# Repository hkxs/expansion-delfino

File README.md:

# expansion-delfino
Tarjeta de expansión para el launchpad LAUNCHXL-F28377S

Para un tutorial rápido sobre el MCU TMS320F28377S se puede consultar:

http://odin.fi-b.unam.mx/labdsp/files/ADSP/apuntes/Tutorial_VF.pdf

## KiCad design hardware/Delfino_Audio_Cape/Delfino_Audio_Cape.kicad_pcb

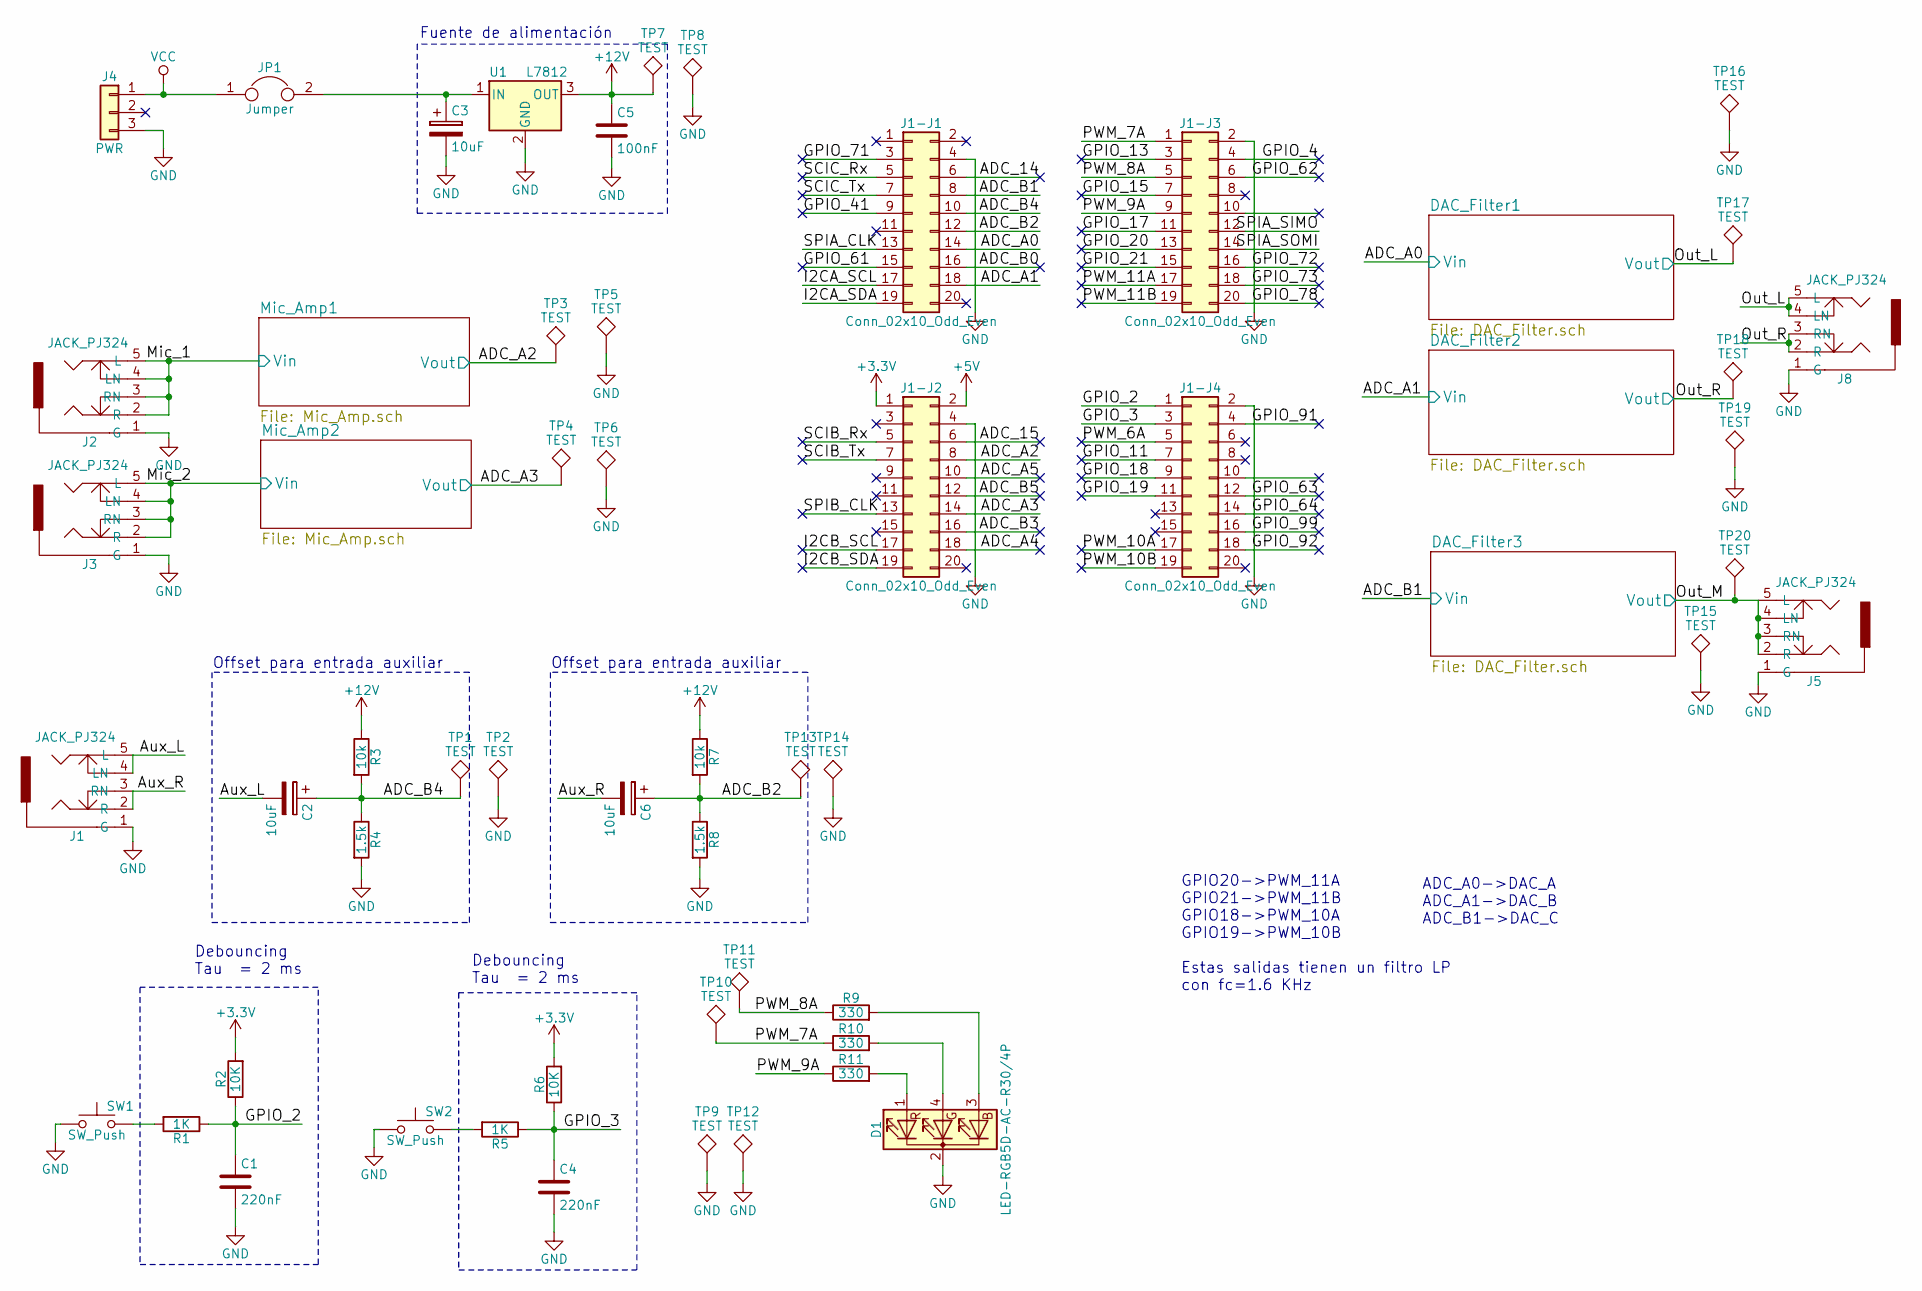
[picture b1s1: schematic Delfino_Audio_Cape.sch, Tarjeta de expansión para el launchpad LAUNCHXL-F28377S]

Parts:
C1, C4: 220nF; C_Disc_D4.3mm_W1.9mm_P5.00mm
C2, C3, C6: 10uF; CP_Radial_D6.3mm_P2.50mm
C5: 100nF; C_Disc_D4.3mm_W1.9mm_P5.00mm
D1: LED-RGB5D-AC-R30/4P; LED_D5.0mm-4
J1, J2, J3, J5, J8: JACK_PJ324; PJ-324
J1-J1, J1-J2, J1-J3, J1-J4: Conn_02x10_Odd_Even; Pin_Header_Straight_2x10_Pitch2.54mm
J4: PWR; bornier3
JP1: Jumper; Pin_Header_Straight_1x02_Pitch2.54mm
R1, R5: 1K; R_Axial_DIN0207_L6.3mm_D2.5mm_P10.16mm_Horizontal
R2, R6: 10K; R_Axial_DIN0207_L6.3mm_D2.5mm_P10.16mm_Horizontal
R3, R7: 10k; R_Axial_DIN0207_L6.3mm_D2.5mm_P10.16mm_Horizontal
R4, R8: 1.5k; R_Axial_DIN0207_L6.3mm_D2.5mm_P10.16mm_Horizontal
R9, R10, R11: 330; R_Axial_DIN0207_L6.3mm_D2.5mm_P10.16mm_Horizontal
SW1, SW2: SW_Push; SW_PUSH_6mm
TP1, TP2, TP3, TP4, TP5, TP6, TP7, TP8, TP9, TP10, TP11, TP12, TP13, TP14, TP15, TP16, TP17, TP18, TP19, TP20: TEST; Test_Point_THTPad_4.0x4.0mm_Drill2.0mm
U1: L7812; TO-220_Horizontal

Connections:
+3V3: J1-J2.1, R2.2, R6.2
+5V: J1-J2.2
+12V: C5.1, R3.1, R7.1, TP7.1, U1.3 (OUT); also elsewhere on the board
/ADC_14: J1-J1.6
/ADC_15: J1-J2.6
/ADC_A0: J1-J1.14; also elsewhere on the board
/ADC_A1: J1-J1.18; also elsewhere on the board
/ADC_A2: J1-J2.8, TP3.1; also elsewhere on the board
/ADC_A3: J1-J2.14, TP4.1; also elsewhere on the board
/ADC_A4: J1-J2.18
/ADC_A5: J1-J2.10
/ADC_B0: J1-J1.16
/ADC_B1: J1-J1.8; also elsewhere on the board
/ADC_B2: C6.1, J1-J1.12, R7.2, R8.1, TP13.1
/ADC_B3: J1-J2.16
/ADC_B4: C2.1, J1-J1.10, R3.2, R4.1, TP1.1
/ADC_B5: J1-J2.12
/Aux_L: C2.2, J1.4 (LN), J1.5 (L)
/Aux_R: C6.2, J1.2 (R), J1.3 (RN)
/GPIO_2: C1.1, J1-J4.1, R1.1, R2.1
/GPIO_3: C4.1, J1-J4.3, R5.1, R6.1
/GPIO_4: J1-J3.4
/GPIO_11: J1-J4.7
/GPIO_13: J1-J3.3
/GPIO_15: J1-J3.7
/GPIO_17: J1-J3.11
/GPIO_18: J1-J4.9
/GPIO_19: J1-J4.11
/GPIO_20: J1-J3.13
/GPIO_21: J1-J3.15
/GPIO_41: J1-J1.9
/GPIO_61: J1-J1.15
/GPIO_62: J1-J3.6
/GPIO_63: J1-J4.12
/GPIO_64: J1-J4.14
/GPIO_71: J1-J1.3
/GPIO_72: J1-J3.16
/GPIO_73: J1-J3.18
/GPIO_78: J1-J3.20
/GPIO_91: J1-J4.4
/GPIO_92: J1-J4.18
/GPIO_99: J1-J4.16
/I2CA_SCL: J1-J1.17
/I2CA_SDA: J1-J1.19
/I2CB_SCL: J1-J2.17
/I2CB_SDA: J1-J2.19
/Mic_1: J2.2 (R), J2.3 (RN), J2.4 (LN), J2.5 (L); also elsewhere on the board
/Mic_2: J3.2 (R), J3.3 (RN), J3.4 (LN), J3.5 (L); also elsewhere on the board
/Out_L: J8.4 (LN), J8.5 (L), TP17.1; also elsewhere on the board
/Out_M: J5.2 (R), J5.3 (RN), J5.4 (LN), J5.5 (L), TP20.1; also elsewhere on the board
/Out_R: J8.2 (R), J8.3 (RN), TP18.1; also elsewhere on the board
/PWM_6A: J1-J4.5
/PWM_7A: J1-J3.1, R10.1, TP10.1
/PWM_8A: J1-J3.5, R9.1, TP11.1
/PWM_9A: J1-J3.9, R11.1
/PWM_10A: J1-J4.17
/PWM_10B: J1-J4.19
/PWM_11A: J1-J3.17
/PWM_11B: J1-J3.19
/SCIB_Rx: J1-J2.5
/SCIB_Tx: J1-J2.7
/SCIC_Rx: J1-J1.5
/SCIC_Tx: J1-J1.7
/SPIA_CLK: J1-J1.13
/SPIA_SIMO: J1-J3.12
/SPIA_SOMI: J1-J3.14
/SPIB_CLK: J1-J2.13
GND: C1.2, C3.2, C4.2, C5.2, D1.2 (K), J1.1 (G), J1-J1.4, J1-J2.4, J1-J3.2, J1-J4.2, J2.1 (G), J3.1 (G), J4.3, J5.1 (G), J8.1 (G), R4.2, R8.2, SW1.1, SW2.1, TP2.1, TP5.1, TP6.1, TP8.1, TP9.1, TP12.1, TP14.1, TP15.1, TP16.1, TP19.1, U1.2 (GND); also elsewhere on the board
unnamed: C3.1, JP1.2, U1.1 (IN)
unnamed: D1.1 (RA), R11.2
unnamed: D1.3 (BA), R9.2
unnamed: D1.4 (GA), R10.2
unnamed: R1.2, SW1.2
unnamed: R5.2, SW2.2
VCC: J4.1, JP1.1

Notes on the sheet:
ADC_A0->DAC_A ADC_A1->DAC_B ADC_B1->DAC_C
GPIO20->PWM_11A GPIO21->PWM_11B GPIO18->PWM_10A GPIO19->PWM_10B Estas salidas tienen un filtro LP con fc=1.6 KHz
Debouncing Tau = 2 ms
Offset para entrada auxiliar
Fuente de alimentación

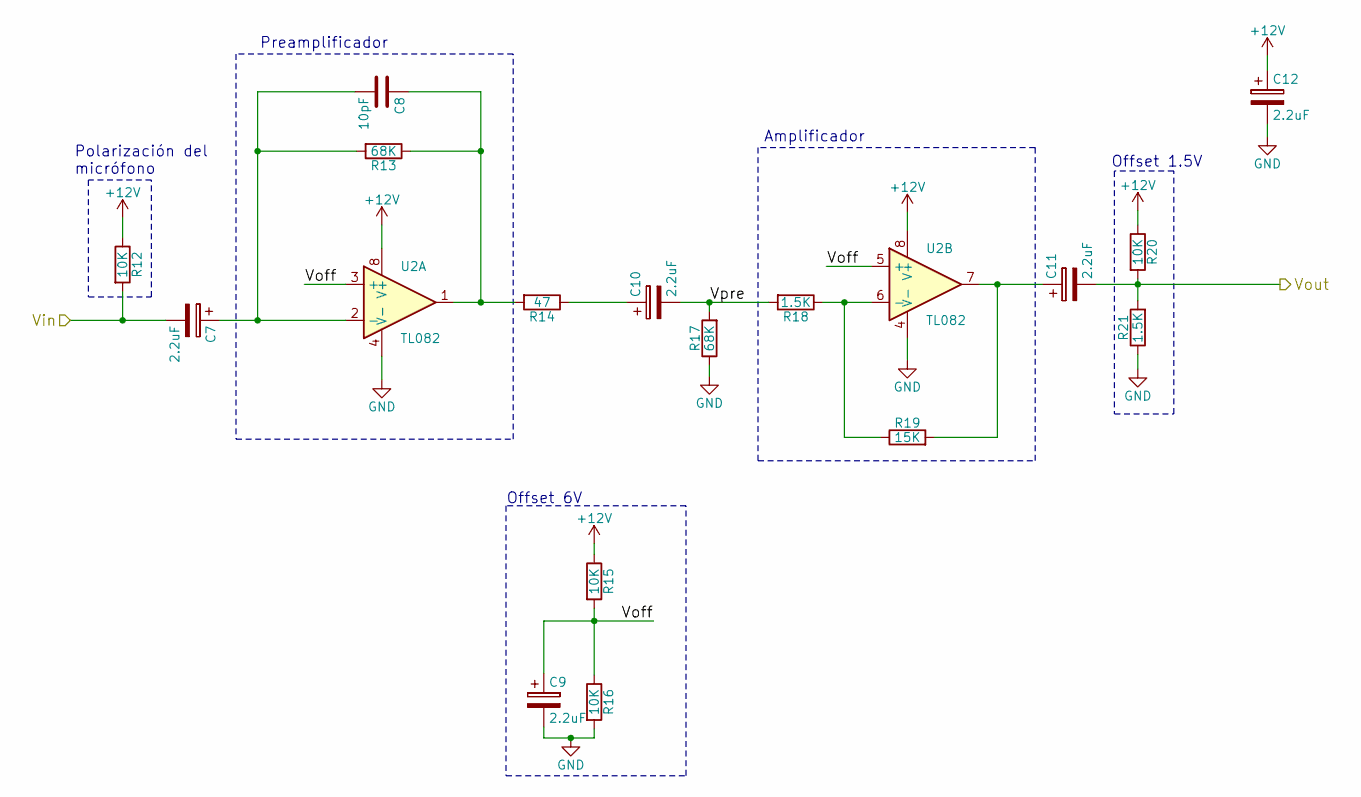
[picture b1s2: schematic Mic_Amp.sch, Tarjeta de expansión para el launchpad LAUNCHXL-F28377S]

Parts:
C7, C9, C10, C11, C12: 2.2uF; CP_Radial_D6.3mm_P2.50mm
C8: 10pF; C_Disc_D4.3mm_W1.9mm_P5.00mm
R12, R15, R16, R20: 10K; R_Axial_DIN0207_L6.3mm_D2.5mm_P10.16mm_Horizontal
R13, R17: 68K; R_Axial_DIN0207_L6.3mm_D2.5mm_P10.16mm_Horizontal
R14: 47; R_Axial_DIN0207_L6.3mm_D2.5mm_P10.16mm_Horizontal
R18, R21: 1.5K; R_Axial_DIN0207_L6.3mm_D2.5mm_P10.16mm_Horizontal
R19: 15K; R_Axial_DIN0207_L6.3mm_D2.5mm_P10.16mm_Horizontal
U2: TL082; DIP-8_W7.62mm_LongPads

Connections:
+12V: C12.1, R12.1, R15.1, R20.1, U2.8 (V+); also elsewhere on the board
/ADC_A2: C11.2, R20.2, R21.2; also elsewhere on the board
/Mic_1: C7.2, R12.2; also elsewhere on the board
/Mic_Amp1/Voff: C9.1, R15.2, R16.1, U2.3 (+), U2.5 (+)
/Mic_Amp1/Vpre: C10.2, R17.2, R18.2
GND: C9.2, C12.2, R16.2, R17.1, R21.1, U2.4 (V-); also elsewhere on the board
unnamed: C7.1, C8.2, R13.2, U2.2 (-)
unnamed: C8.1, R13.1, R14.2, U2.1
unnamed: C10.1, R14.1
unnamed: C11.1, R19.2, U2.7
unnamed: R18.1, R19.1, U2.6 (-)

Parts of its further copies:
C13, C15, C16, C17, C18: 2.2uF; CP_Radial_D6.3mm_P2.50mm
C14: 10pF; C_Disc_D4.3mm_W1.9mm_P5.00mm
R22, R25, R26, R30: 10K; R_Axial_DIN0207_L6.3mm_D2.5mm_P10.16mm_Horizontal
R23, R27: 68K; R_Axial_DIN0207_L6.3mm_D2.5mm_P10.16mm_Horizontal
R24: 47; R_Axial_DIN0207_L6.3mm_D2.5mm_P10.16mm_Horizontal
R28, R31: 1.5K; R_Axial_DIN0207_L6.3mm_D2.5mm_P10.16mm_Horizontal
R29: 15K; R_Axial_DIN0207_L6.3mm_D2.5mm_P10.16mm_Horizontal
U3: TL082; DIP-8_W7.62mm_LongPads

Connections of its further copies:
+12V: C18.1, R22.1, R25.1, R30.1, U3.8 (V+); also elsewhere on the board
/ADC_A3: C17.2, R30.2, R31.2; also elsewhere on the board
/Mic_2: C13.2, R22.2; also elsewhere on the board
/Mic_Amp2/Voff: C15.1, R25.2, R26.1, U3.3 (+), U3.5 (+)
/Mic_Amp2/Vpre: C16.2, R27.2, R28.2
GND: C15.2, C18.2, R26.2, R27.1, R31.1, U3.4 (V-); also elsewhere on the board
unnamed: C13.1, C14.2, R23.2, U3.2 (-)
unnamed: C14.1, R23.1, R24.2, U3.1
unnamed: C16.1, R24.1
unnamed: C17.1, R29.2, U3.7
unnamed: R28.1, R29.1, U3.6 (-)

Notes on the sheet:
Offset 6V
Polarización del micrófono
Offset 1.5V
Preamplificador
Amplificador

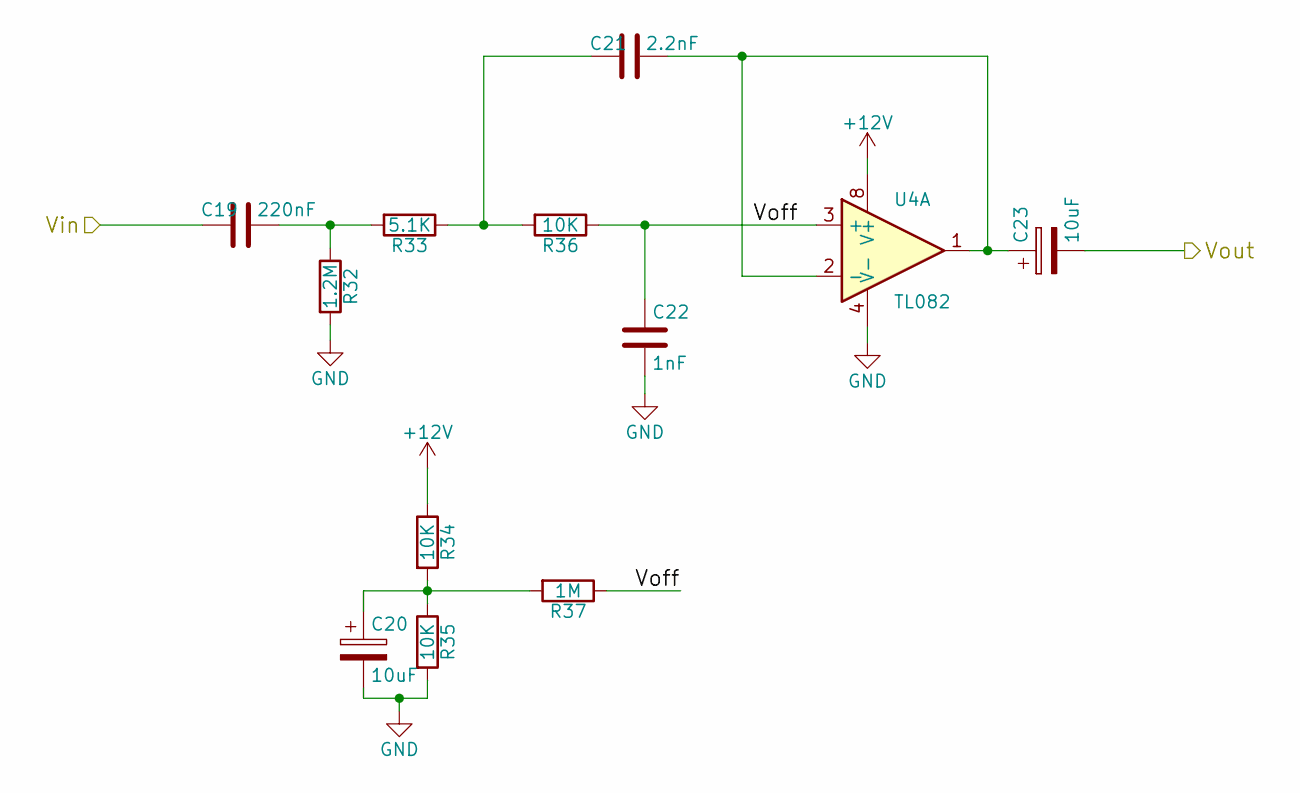
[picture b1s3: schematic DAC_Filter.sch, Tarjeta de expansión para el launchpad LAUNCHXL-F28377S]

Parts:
C19: 220nF; C_Disc_D4.3mm_W1.9mm_P5.00mm
C20, C23: 10uF; CP_Radial_D6.3mm_P2.50mm
C21: 2.2nF; C_Disc_D4.3mm_W1.9mm_P5.00mm
C22: 1nF; C_Disc_D4.3mm_W1.9mm_P5.00mm
R32: 1.2M; R_Axial_DIN0207_L6.3mm_D2.5mm_P10.16mm_Horizontal
R33: 5.1K; R_Axial_DIN0207_L6.3mm_D2.5mm_P10.16mm_Horizontal
R34, R35, R36: 10K; R_Axial_DIN0207_L6.3mm_D2.5mm_P10.16mm_Horizontal
R37: 1M; R_Axial_DIN0207_L6.3mm_D2.5mm_P10.16mm_Horizontal
U4: TL082; DIP-8_W7.62mm_LongPads

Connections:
+12V: R34.1, U4.8 (V+); also elsewhere on the board
/ADC_A0: C19.2; also elsewhere on the board
/DAC_Filter1/Voff: C22.1, R36.1, R37.1, U4.3 (+)
/DAC_Filter2/Voff: U4.5 (+); also elsewhere on the board
/Out_L: C23.2; also elsewhere on the board
GND: C20.2, C22.2, R32.2, R35.2, U4.4 (V-); also elsewhere on the board
unnamed: C19.1, R32.1, R33.2
unnamed: C20.1, R34.2, R35.1, R37.2
unnamed: C21.1, C23.1, U4.1, U4.2 (-)
unnamed: C21.2, R33.1, R36.2
unnamed 90: U4.6 (-), U4.7; also elsewhere on the board

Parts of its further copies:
C24, C29: 220nF; C_Disc_D4.3mm_W1.9mm_P5.00mm
C25, C28, C30, C33: 10uF; CP_Radial_D6.3mm_P2.50mm
C26, C31: 2.2nF; C_Disc_D4.3mm_W1.9mm_P5.00mm
C27, C32: 1nF; C_Disc_D4.3mm_W1.9mm_P5.00mm
R38, R44: 1.2M; R_Axial_DIN0207_L6.3mm_D2.5mm_P10.16mm_Horizontal
R39, R45: 5.1K; R_Axial_DIN0207_L6.3mm_D2.5mm_P10.16mm_Horizontal
R40, R41, R42, R46, R47, R48: 10K; R_Axial_DIN0207_L6.3mm_D2.5mm_P10.16mm_Horizontal
R43, R49: 1M; R_Axial_DIN0207_L6.3mm_D2.5mm_P10.16mm_Horizontal
U5: TL082; DIP-8_W7.62mm_LongPads

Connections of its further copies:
+12V: R40.1, R46.1, U5.8 (V+); also elsewhere on the board
/ADC_A1: C24.2; also elsewhere on the board
/ADC_B1: C29.2; also elsewhere on the board
/DAC_Filter2/Voff: C27.1, R42.1, R43.1; also elsewhere on the board
/DAC_Filter3/Voff: C32.1, R48.1, R49.1, U5.3 (+)
/Out_M: C33.2; also elsewhere on the board
/Out_R: C28.2; also elsewhere on the board
GND: C25.2, C27.2, C30.2, C32.2, R38.2, R41.2, R44.2, R47.2, U5.4 (V-); also elsewhere on the board
unnamed: C24.1, R38.1, R39.2
unnamed: C25.1, R40.2, R41.1, R43.2
unnamed 90: C26.1, C28.1; also elsewhere on the board
unnamed: C26.2, R39.1, R42.2
unnamed: C29.1, R44.1, R45.2
unnamed: C30.1, R46.2, R47.1, R49.2
unnamed: C31.1, C33.1, U5.1, U5.2 (-)
unnamed: C31.2, R45.1, R48.2

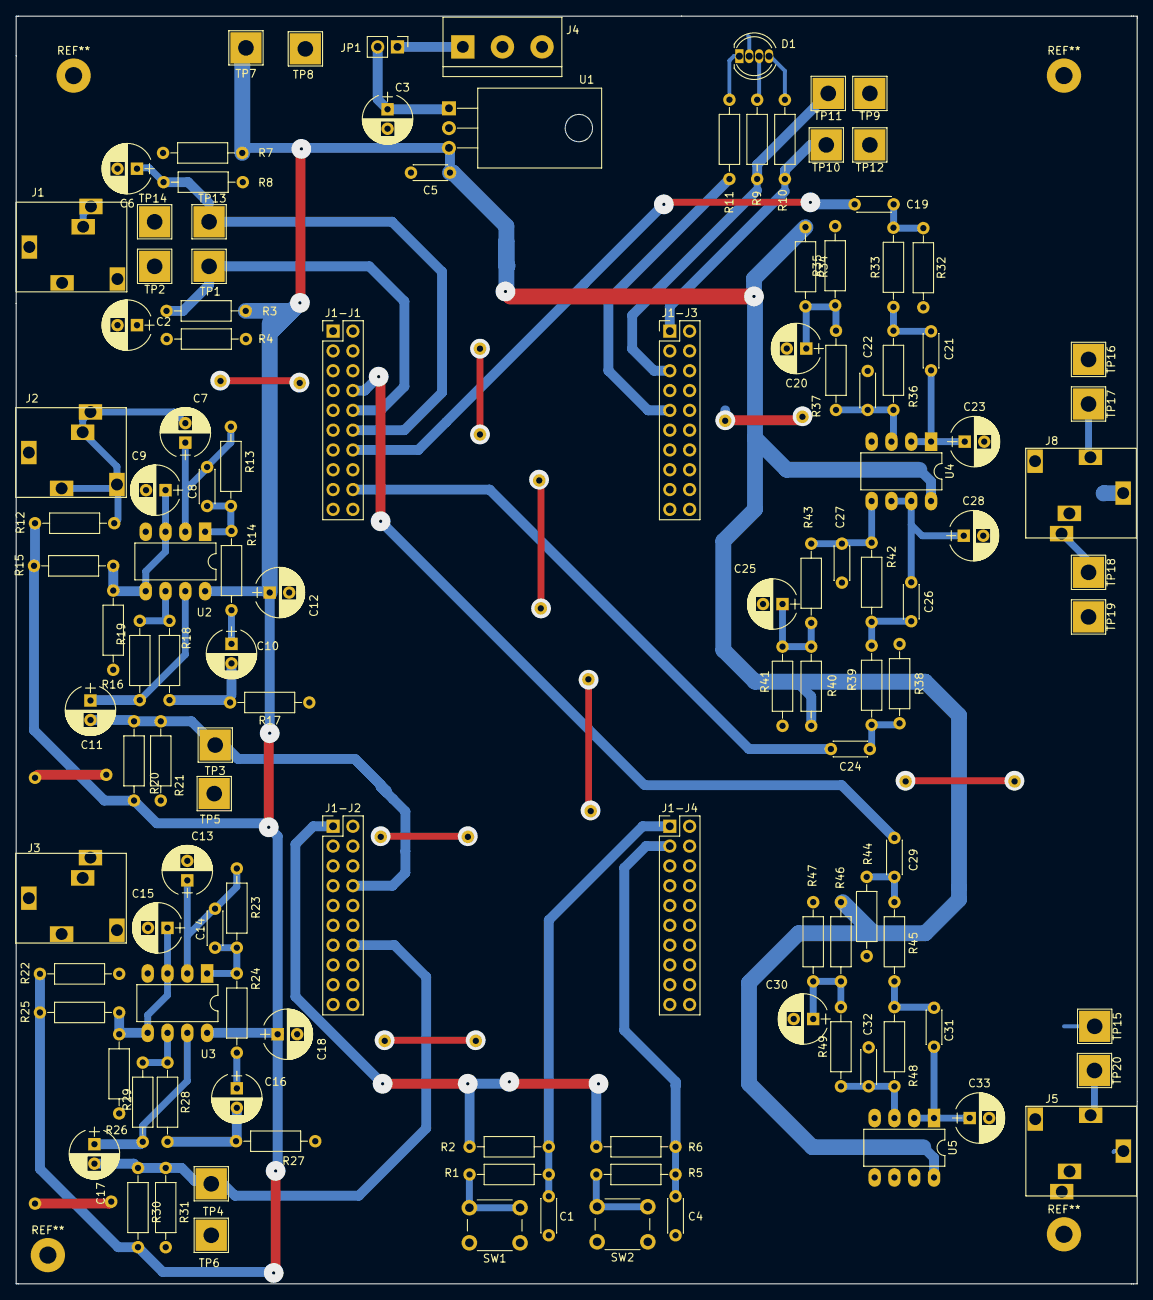
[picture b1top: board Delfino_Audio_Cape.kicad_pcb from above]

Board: 2 copper layers, 143.8 x 162.6 mm, 121 parts (0 on the bottom side), 58 nets.

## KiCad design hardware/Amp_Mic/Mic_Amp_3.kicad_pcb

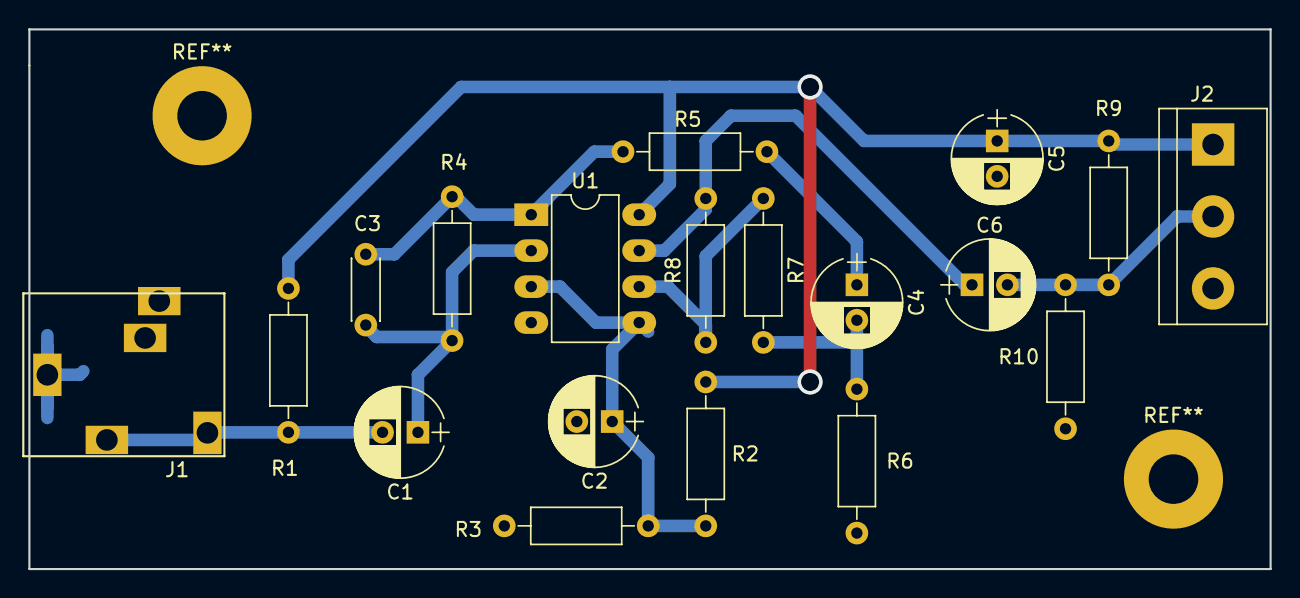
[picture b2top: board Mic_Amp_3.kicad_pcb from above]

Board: 2 copper layers, 87.6 x 38.1 mm, 19 parts (0 on the bottom side), 11 nets.

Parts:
C1, C2, C4, C5, C6: 2.2uF; CP_Radial_D6.3mm_P2.50mm
C3: 10pF; C_Disc_D4.3mm_W1.9mm_P5.00mm
J1: JACK_PJ324; PJ-324
J2: CONN_01X03; bornier3
R1, R2, R3, R9: 10K; R_Axial_DIN0207_L6.3mm_D2.5mm_P10.16mm_Horizontal
R4, R6: 68K; R_Axial_DIN0207_L6.3mm_D2.5mm_P10.16mm_Horizontal
R5: 47; R_Axial_DIN0207_L6.3mm_D2.5mm_P10.16mm_Horizontal
R7, R8, R10: 1.5K; R_Axial_DIN0207_L6.3mm_D2.5mm_P10.16mm_Horizontal
U1: TL082; DIP-8_W7.62mm_LongPads

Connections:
+12V: C5.1, J2.1, R1.1, R2.1, R9.1, U1.8
/Vin: C1.2, J1.4, J1.5, R1.2
/Voff: C2.1, R2.2, R3.1, U1.3, U1.5
/Vout: C6.2, J2.2, R9.2, R10.2
/Vpre: C4.2, R6.2, R7.2
GND: C2.2, C5.2, J1.1, J2.3, R3.2, R6.1, R10.1, U1.4
unnamed: C1.1, C3.2, R4.2, U1.2
unnamed: C3.1, R4.1, R5.2, U1.1
unnamed: C4.1, R5.1
unnamed: C6.1, R8.2, U1.7
unnamed: R7.1, R8.1, U1.6

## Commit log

2017-08-16 CMD genérico para ejecutar programas desde RAM
2017-08-16 Libreria para manejo del sistema analógico
2017-08-16 Libreria para usar el puerto UART
2017-08-17 Ejemplo de uso del subsistema analógico
2017-08-17 Ejemplo de uso de la FFT
2017-08-17 Ejemplo de uso del PWM en esamblador
2017-08-17 Ejemplo para la tarjeta de evaluación del laboratorio
2017-08-17 Ejemplo de uso de timer en ensamblador
2017-08-17 Ejemplo de uso de timer
2017-08-17 Ejemplo de uso del puerto serial
2017-08-17 CMD genérico para ejecutar programas desde FLASH
2017-08-17 Ejemplo uso de GPIO
2017-08-17 Ejemplo uso de GPIO en ensamblador
2017-08-17 Amplificador para micrófono electret
2017-08-17 Notas para fabricación
2017-08-17 Fuente boost simple
2017-08-17 Notas
2017-08-17 Filtro paso bajas a 20KHz para el DAC
2017-08-29 Proyecto y simulaciones del filtro para el DAC
2017-09-06 Ejemplo de configuración del puerto SPI
2017-09-14 Boosterpack de audio para la Delfino
2017-09-15 LP project
2017-09-21 Avances de la tarjeta de expansión
2017-09-25 Avances en tarjeta de expansión
2017-09-26 Avances en el PCB
2017-09-26 Se genero parte de la documentación de la tarjeta
2017-10-09 Cambios en el PCB
2017-10-26 Cambios en el PCB de la tarjeta de expansión
